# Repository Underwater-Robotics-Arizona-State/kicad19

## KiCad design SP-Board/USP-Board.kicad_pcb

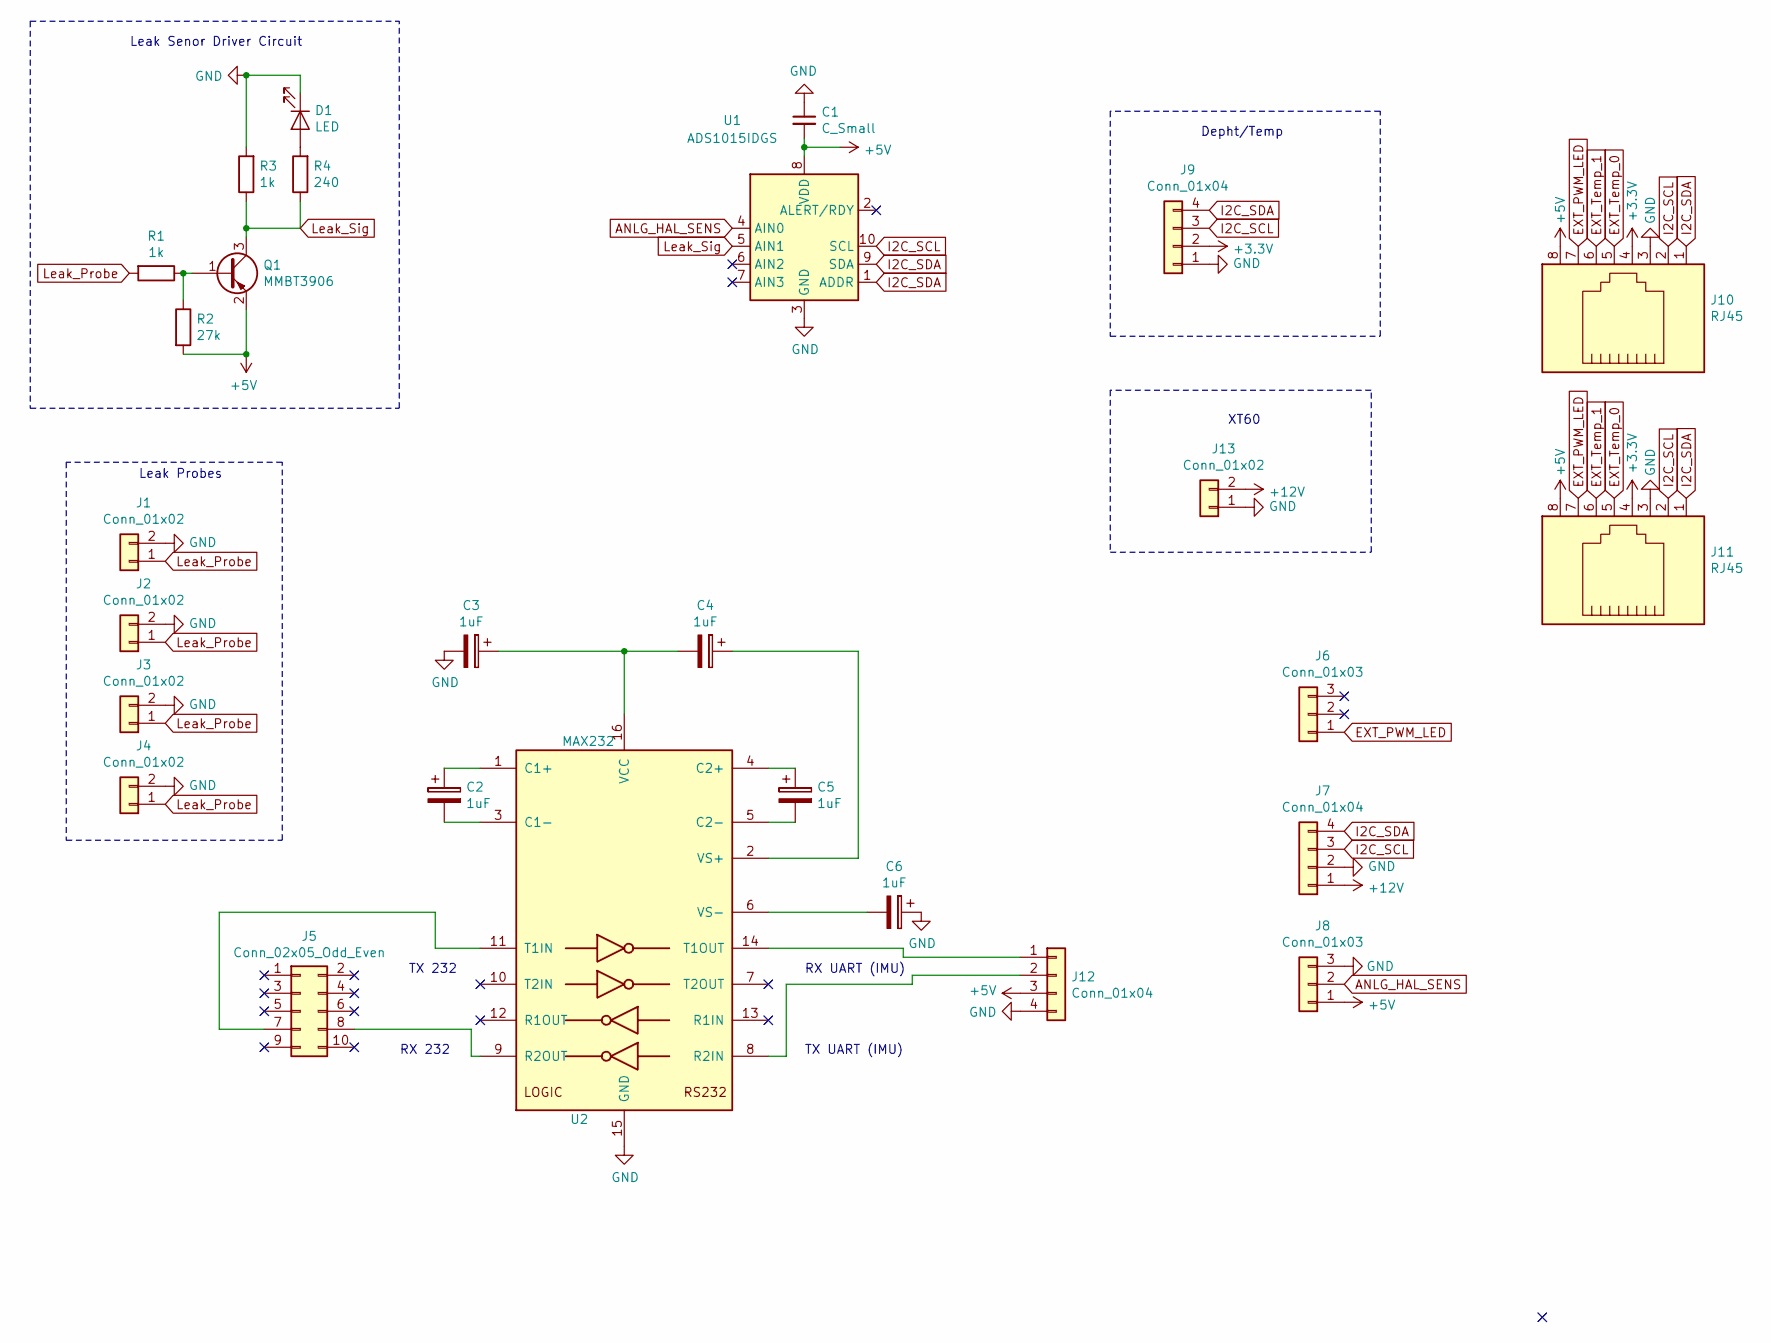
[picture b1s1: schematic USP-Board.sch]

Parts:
C1: C_Small; CP_EIA-1608-08_AVX-J_Pad1.25x1.05mm_HandSolder
C2, C3, C4, C5, C6: 1uF; CP_EIA-1608-08_AVX-J_Pad1.25x1.05mm_HandSolder
D1: LED; LED_0603_1608Metric
J1, J2, J3, J4: Conn_01x02; PinHeader_1x02_P2.54mm_Vertical
J5: Conn_02x05_Odd_Even; Amphenol 98424-G52-10LF
J6, J8: Conn_01x03; PinHeader_1x03_P2.54mm_Vertical
J7, J9, J12: Conn_01x04; PinHeader_1x04_P2.54mm_Vertical
J10, J11: RJ45; RJ45_8
J13: Conn_01x02; XT60
Q1: MMBT3906; SOT-23
R1, R3: 1k; R_1206_3216Metric_Pad1.42x1.75mm_HandSolder
R2: 27k; R_1206_3216Metric_Pad1.42x1.75mm_HandSolder
R4: 240; R_1206_3216Metric_Pad1.42x1.75mm_HandSolder
U1: ADS1015IDGS; TSSOP-10_3x3mm_P0.5mm
U2: MAX232; SOIC-16_3.9x9.9mm_P1.27mm

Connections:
+3V3: J9.2, J10.4, J11.4
+5V: C1.2, J8.1, J10.8, J11.8, J12.3, Q1.2 (E), R2.2, U1.8 (VDD)
+12V: J7.1, J13.2
ANLG_HAL_SENS: J8.2, U1.4 (AIN0)
EXT_PWM_LED: J6.1, J10.7, J11.7
EXT_Temp_0: J10.5, J11.5
EXT_Temp_1: J10.6, J11.6
GND: C1.1, C3.2, C6.1, D1.1 (K), J1.2, J2.2, J3.2, J4.2, J7.2, J8.3, J9.1, J10.3, J11.3, J12.4, J13.1, R3.2, U1.3 (GND), U2.15 (GND)
I2C_SCL: J7.3, J9.3, J10.2, J11.2, U1.10 (SCL)
I2C_SDA: J7.4, J9.4, J10.1, J11.1, U1.1 (ADDR), U1.9 (SDA)
Leak_Probe: J1.1, J2.1, J3.1, J4.1, R1.2
Leak_Sig: Q1.3 (C), R3.1, R4.1, U1.5 (AIN1)
unnamed: C2.1, U2.1 (C1+)
unnamed: C2.2, U2.3 (C1-)
unnamed: C3.1, C4.2, U2.16 (VCC)
unnamed: C4.1, U2.2 (VS+)
unnamed: C5.1, U2.4 (C2+)
unnamed: C5.2, U2.5 (C2-)
unnamed: C6.2, U2.6 (VS-)
unnamed: D1.2 (A), R4.2
unnamed: J5.7, U2.11 (T1IN)
unnamed: J5.8, U2.9 (R2OUT)
unnamed: J12.1, U2.14 (T1OUT)
unnamed: J12.2, U2.8 (R2IN)
unnamed: Q1.1 (B), R1.1, R2.1

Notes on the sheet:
Leak Senor Driver Circuit
Depht/Temp
XT60
Leak Probes
TX 232
RX 232
TX UART (IMU)
RX UART (IMU)

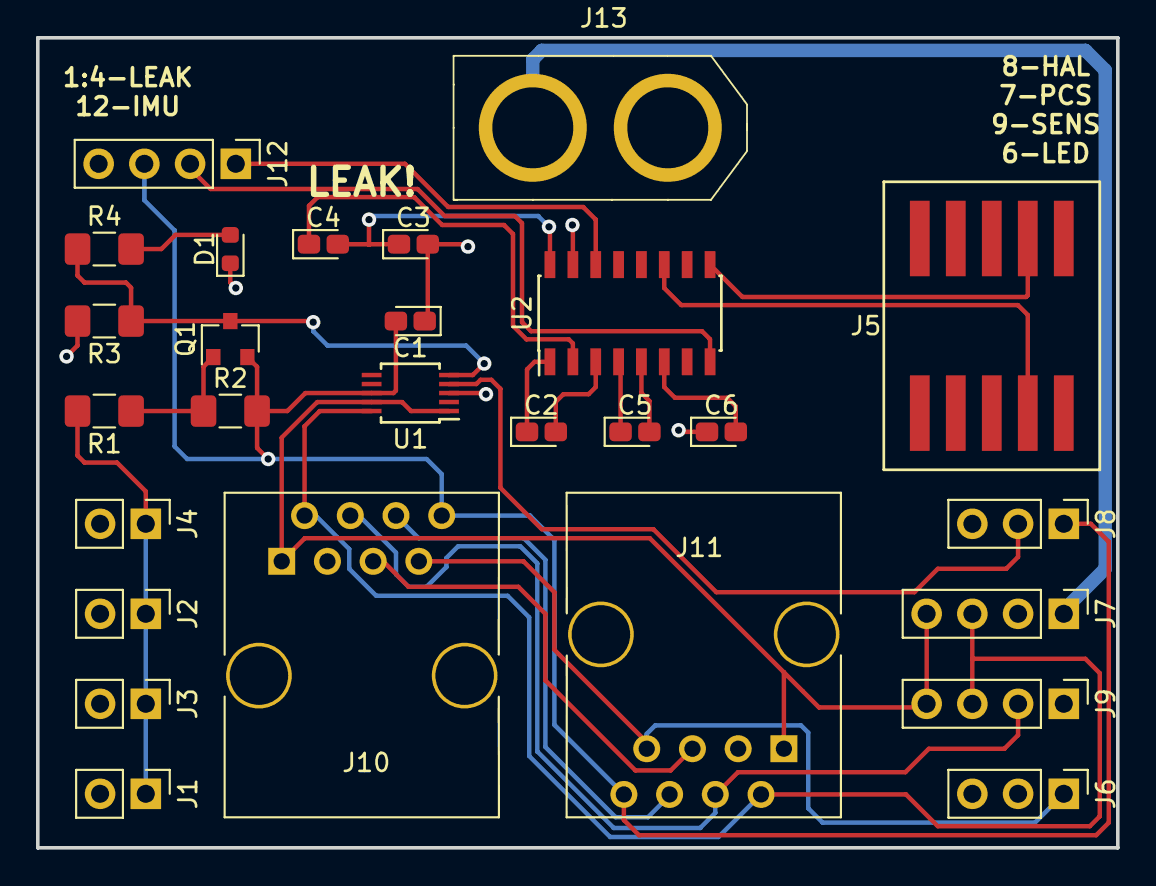
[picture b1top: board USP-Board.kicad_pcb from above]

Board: 2 copper layers, 60.0 x 45.0 mm, 27 parts (0 on the bottom side), 25 nets.

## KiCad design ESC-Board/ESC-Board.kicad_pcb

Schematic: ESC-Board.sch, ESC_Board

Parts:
A1: Arduino_Nano_v3.x; Arduino_Nano
F1, F2, F3, F4: 10/15; Fuse_SMD1206_HandSoldering
F5: 500m; Fuse_SMD1206_HandSoldering
I1, I2: RJ45; RJ45_8
J1, J2: Molex; Molex_6pin
J3: XT_60; XT60
MH1, MH2, MH3, MH4: MountingHole; MountingHole_3.2mm_M3
R1, R2: R; R_0805
U1, U2, U3, U4: ACS780xLRTR-100U; Allegro_PSOF-7_4.8x6.4mm_Pitch1.60mm
U5, U6, U7, U8: ESC:Blue_ESC; Blue_ESC
U9, U10: TMP235A2DBZT; SOT-23

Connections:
+3V3: A1.17, I1.4, I2.4, R1.1, R2.2, U9.1, U10.1
+5V: A1.27, I1.8, I2.8, U1.1 (VCC), U2.1 (VCC), U3.1 (VCC), U4.1 (VCC)
+12V: F1.2, F2.2, F3.2, F4.2, F5.1, J3.1
Current_A0: A1.21, U1.3 (VOUT)
Current_A1: A1.22, U2.3 (VOUT)
Current_A2: A1.23, U3.3 (VOUT)
Current_A3: A1.24, U4.3 (VOUT)
EXT_PWM_LED: A1.14, I1.7, I2.7
Ext_Temp_0: A1.26, I1.5, I2.5
Ext_Temp_1: A1.25, I1.6, I2.6
GND: A1.4, A1.29, I1.3, I2.3, J3.2, U1.2 (GND), U2.2 (GND), U3.2 (GND), U4.2 (GND), U5.2, U5.7, U6.2, U6.7, U7.2, U7.7, U8.2, U8.7, U9.3, U10.3
I2C_SCL: A1.8, I1.2, I2.2, R2.1
I2C_SDA: A1.7, I1.1, I2.1, R1.2
unnamed: A1.30, F5.2
unnamed: F1.1, U1.6 (IP-)
unnamed: F2.1, U2.6 (IP-)
unnamed: F3.1, U3.6 (IP-)
unnamed: F4.1, U4.6 (IP-)
unnamed: J1.1, U5.5
unnamed: J1.2, U5.4
unnamed: J1.3, U5.3
unnamed: J1.4, U6.5
unnamed: J1.5, U6.4
unnamed: J1.6, U6.3
unnamed: J2.1, U7.5
unnamed: J2.2, U7.4
unnamed: J2.3, U7.3
unnamed: J2.4, U8.5
unnamed: J2.5, U8.4
unnamed: J2.6, U8.3
PWM_ESC_1: A1.13, U8.6
PWM_ESC_2: A1.12, U7.6
PWM_ESC_3: A1.9, U6.6
PWM_ESC_4: A1.6, U5.6
Power_ESC_1: U1.5 (IP+), U8.1
Power_ESC_2: U2.5 (IP+), U7.1
Power_ESC_3: U3.5 (IP+), U6.1
Power_ESC_4: U4.5 (IP+), U5.1
Temp_A4: A1.20, U9.2
Temp_A5: A1.19, U10.2

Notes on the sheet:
Power Connector
Ardunio Nano
I2C RJ45 Connector
Current Monintoring
ESC to Connectors
Mounting Holes
Tempure Sensors

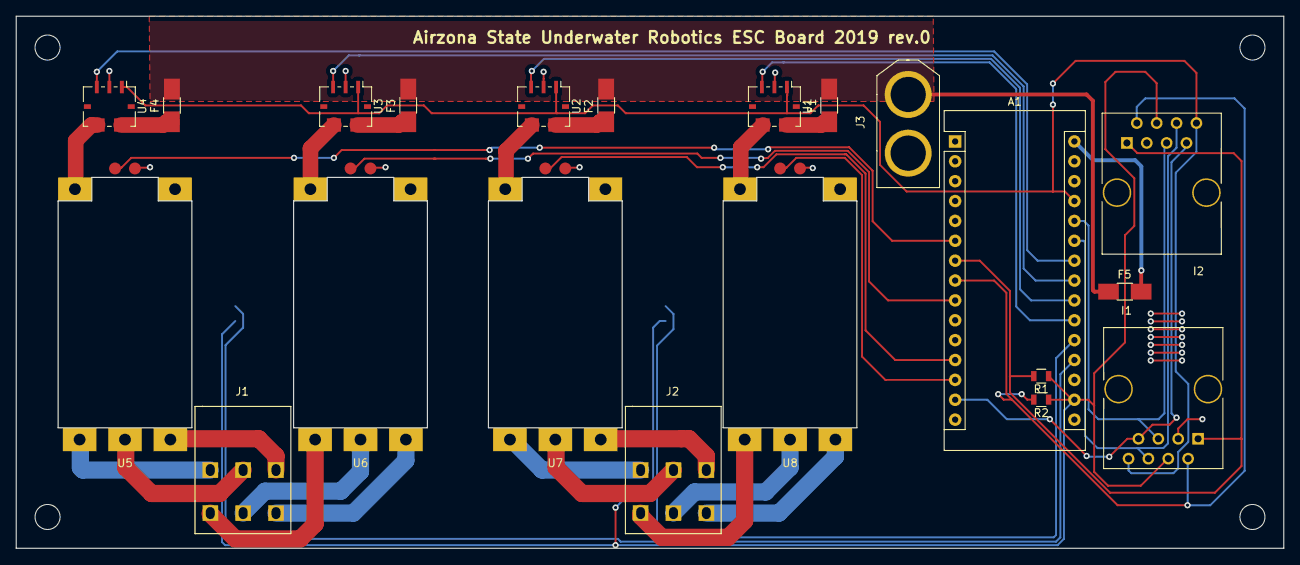
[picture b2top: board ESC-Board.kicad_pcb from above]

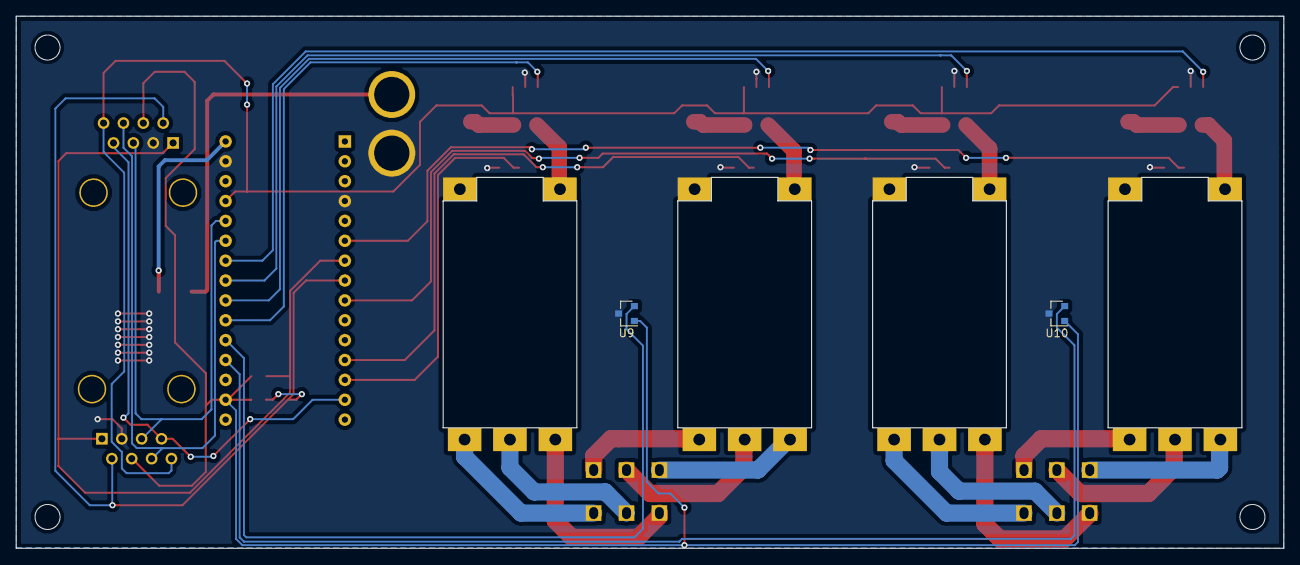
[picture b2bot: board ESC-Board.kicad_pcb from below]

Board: 2 copper layers, 162.0 x 68.0 mm, 28 parts (2 on the bottom side), 40 nets.

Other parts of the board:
 MH3: MountingHole; MountingHole_3.2mm_M3

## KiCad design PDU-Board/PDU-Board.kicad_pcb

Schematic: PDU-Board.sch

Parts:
J0: Main Feed; XT60
J1: Motor-1; XT60
J2: Motor-2; XT60
J3: Mother Board; XT60
J4, J5: RJ45; RJ45_8
U1, U2, U3, U4: VICOR-DC-DC; VICOR_VIA_DCM3414
U5, U6: ESC:TMP235A2DBZT; SOT-23

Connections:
48v_GND: J0.2, U1.2, U2.2, U3.2, U4.2
+3V3: J4.4, J5.4, U5.1, U6.1
+12V: J1.1, J2.1, J3.1, U1.3, U2.3, U3.3, U4.3
+48V: J0.1, U1.1, U2.1, U3.1, U4.1
Ext_Temp_0: J4.5, J5.5, U6.2
Ext_Temp_1: J4.6, J5.6, U5.2
GND: J1.2, J2.2, J3.2, J4.3, J5.3, U1.4, U2.4, U3.4, U4.4, U5.3, U6.3
unnamed: J4.1, J5.1
unnamed: J4.2, J5.2
unnamed: J4.8, J5.8
Water_Sensor: J4.7, J5.7

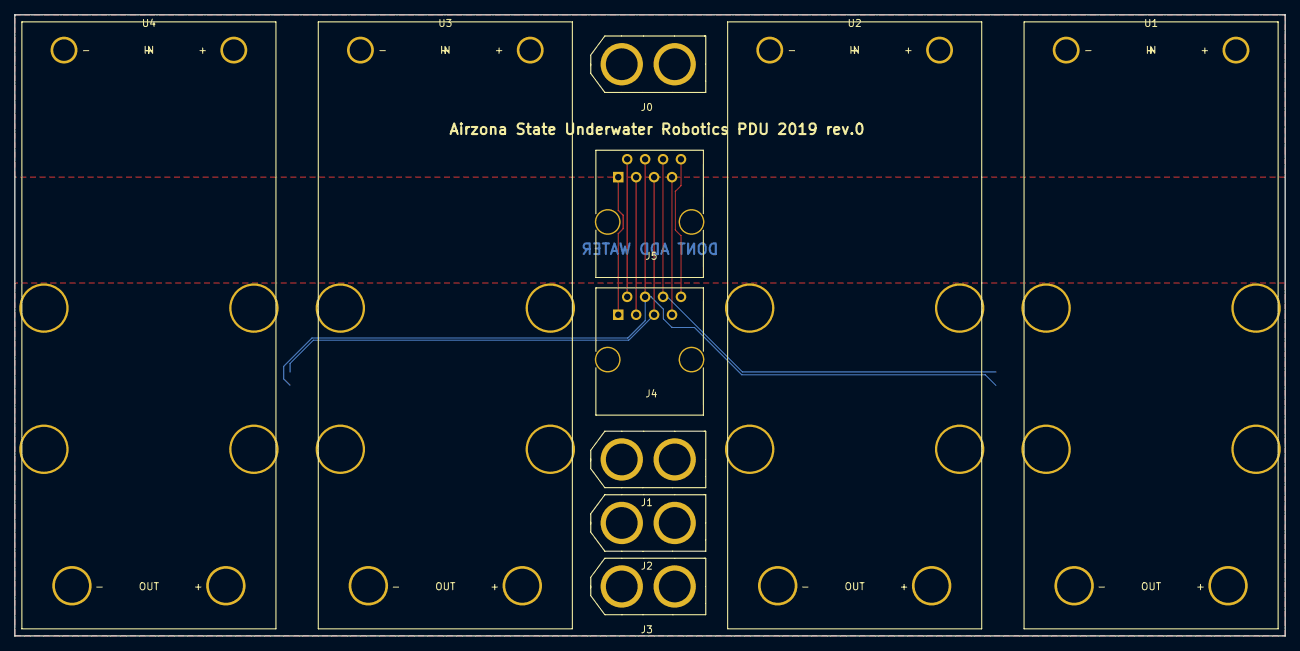
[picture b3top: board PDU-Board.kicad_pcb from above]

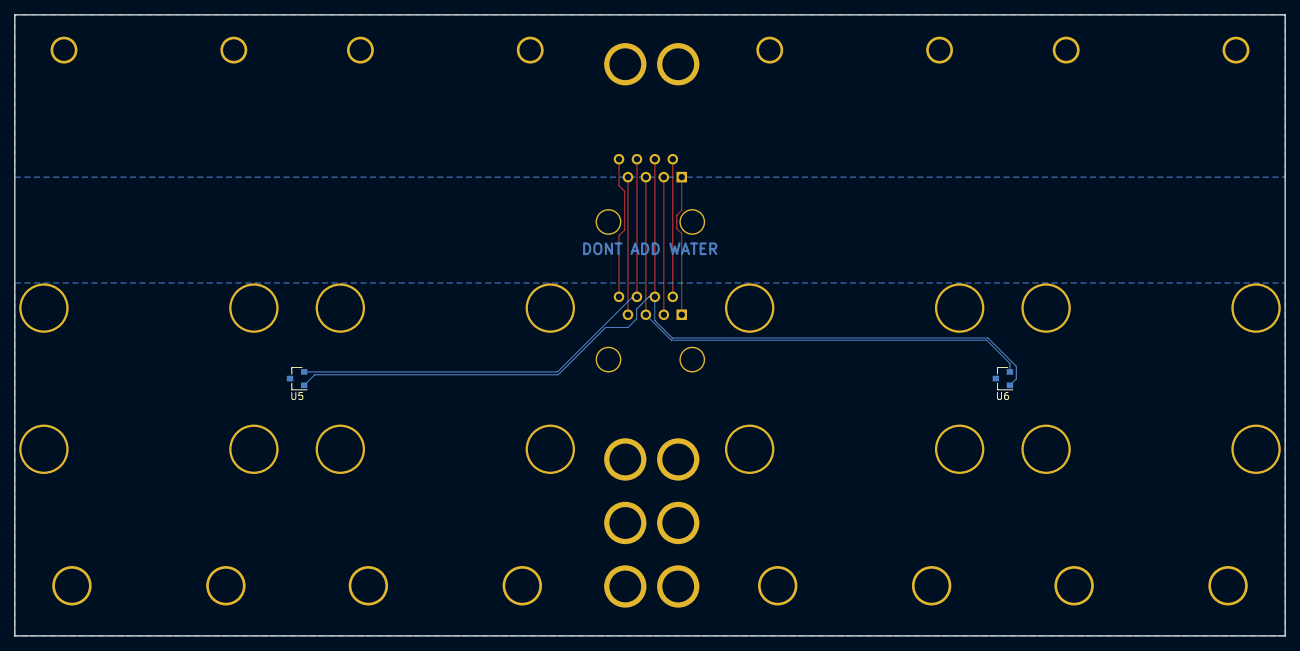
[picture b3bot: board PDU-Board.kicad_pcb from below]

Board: 2 copper layers, 180.0 x 88.0 mm, 12 parts (2 on the bottom side), 11 nets.

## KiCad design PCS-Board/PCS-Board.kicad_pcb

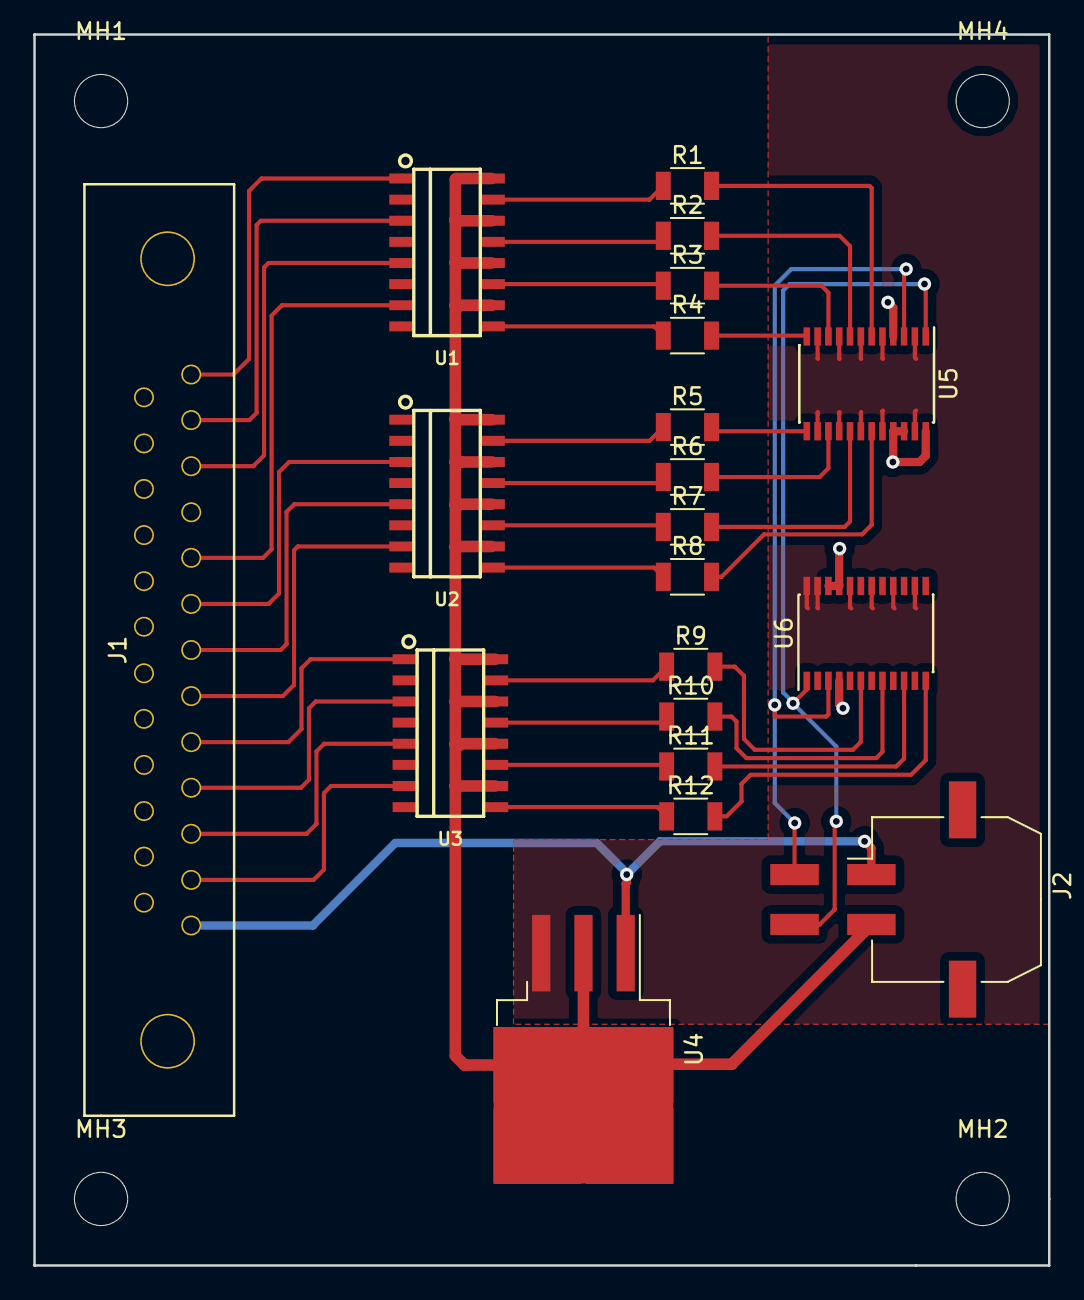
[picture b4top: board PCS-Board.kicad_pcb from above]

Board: 2 copper layers, 61.0 x 74.0 mm, 24 parts (0 on the bottom side), 40 nets.

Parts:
J1: DB25_Female_MountingHoles; Dsub 25pin
J2: Conn_01x04; Molex_MicroFit_3.0-43045-0410_04x3.00mm_Angled
MH1, MH2, MH3, MH4: MountingHole; MountingHole_3.2mm_M3
R1, R2, R3, R4, R5, R6, R7, R8, R9, R10, R11, R12: R; R_1206
U1, U2, U3: MMPQ2222A; Soc-16
U4: uA7805; TO-263-3_TabPin2
U5, U6: ADG715; TSSOP-24

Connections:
+5V: U4.3, U5.2, U5.5, U5.7, U5.9, U5.11, U5.14, U5.16, U5.18, U5.20, U5.23, U6.2, U6.5, U6.7, U6.9, U6.11, U6.14, U6.16, U6.18, U6.20, U6.23, U6.24
+12V: J1.13, J2.1, U4.1
GND: J2.2, U1.10, U1.12, U1.14, U1.16, U2.10, U2.12, U2.14, U2.16, U3.10, U3.12, U3.14, U3.16, U4.2, U5.4, U5.21, U5.22, U5.24, U6.4, U6.21, U6.22
I2C_SCL: J2.3, U5.1, U6.1
I2C_SDA: J2.4, U5.3, U6.3
unnamed: R1.1, U1.15
unnamed: R2.1, U1.13
unnamed: R3.1, U1.11
unnamed: R4.1, U1.9
unnamed: R5.1, U2.15
unnamed: R6.1, U2.13
unnamed: R7.1, U2.11
unnamed: R8.1, U2.9
unnamed: R9.1, U3.15
unnamed: R10.1, U3.13
unnamed: R11.1, U3.11
unnamed: R12.1, U3.9
SOLN_EN0: R1.2, U5.6
SOLN_EN1: R2.2, U5.8
SOLN_EN2: R3.2, U5.10
SOLN_EN3: R4.2, U5.12
SOLN_EN4: R5.2, U5.13
SOLN_EN5: R6.2, U5.15
SOLN_EN6: R7.2, U5.17
SOLN_EN7: R8.2, U5.19
SOLN_EN8: R9.2, U6.6
SOLN_EN9: R10.2, U6.8
SOLN_EN10: R11.2, U6.10
SOLN_EN11: R12.2, U6.12
SOLN_PW0: J1.1, U1.1
SOLN_PW1: J1.2, U1.3
SOLN_PW2: J1.3, U1.5
SOLN_PW4: J1.5, U1.7
SOLN_PW5: J1.6, U2.3
SOLN_PW6: J1.7, U2.5
SOLN_PW7: J1.8, U2.7
SOLN_PW8: J1.9, U3.1
SOLN_PW9: J1.10, U3.3
SOLN_PW10: J1.11, U3.5
SOLN_PW11: J1.12, U3.7

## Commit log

2018-12-27 First Upload
2018-12-27 File Path Fix
2018-12-27 colton fix
    schematic issues
2018-12-27 added 3414 and nano footprint and removed gerbers
2018-12-27 little fixes on PDB
2018-12-30 basic fix
2018-12-30 Second Draft (in progress)
    Starting clean up of sch
2018-12-30 Second Draft(In Progress) v2
2018-12-30 Second Draft(in progess) v3
2018-12-30 Second Draft(Final version)
    Alex pls
2018-12-31 Final Draft
2018-12-31 Final Draft(with net list)
2018-12-31 Starting layout
2019-01-03 I hate myself
2019-01-03 OOOF
2019-01-03 Big PP
2019-01-03 Better footprint
    I likey
2019-01-03 Fixed ESC Pwm lines
2019-01-03 More ESC fixes
2019-01-03 ESC Fixes
2019-01-03 Mounting holes
    I did a think
2019-01-03 Layout Draft(Final)
    Needs wires
2019-01-03 Final Layout needs routering
2019-01-03 Foot print fixes
2019-01-03 Added Vicor footprint
    eeeeeeeeeeeeeeeeeeeeeeeeee
2019-01-03 Make Gerberals go bye bye
2019-01-03 PDU Board work
2019-01-04 Board Finalized
    E
2019-01-04 Added Step
2019-01-04 Need current pushed up
2019-01-04 Moved Current sensors up
2019-01-04 ESC board Finalized ready for production
2019-01-04 Fixed names
2019-01-04 Fix issues with ERC
2019-01-04 More fixes on traces
2019-01-04 Fix scmatic
2019-01-05 Fixed issue with scl line
2019-01-05 Begun PDU layout
2019-01-07 temp senors added not finised
2019-01-07 Finalzed Boards ready for production
    YEah
2019-01-08 Added pneumatic files to master
2019-01-08 PCS inital design
2019-01-08 PCS Sch update
2019-01-08 PCS Sch cleanup
    No changes to sch just cleaning it up
2019-01-11 Update to PCS sch
2019-01-11 Fixed Molex hole issue
    Squares dont go in circle holes
2019-01-11 Fix more molex issues
2019-01-11 Forgot to leave fills on
2019-01-18 Add gates
2019-01-18 Alex is big ghey
2019-01-18 Added BJT to SCH
2019-01-18 Fixed RJ 45 connector
2019-01-24 Fixed PDU footprint isuess
    vicor foot print fixed
2019-01-24 Added Drill files and fixed holes
2019-01-24 Add pdu step
2019-01-24 PCS Sch updated with dsub connectorr
2019-01-28 Re designed PDU pre mec spec
2019-01-28 Fixed slik
2019-01-28 Fixed sch on PCS crash
2019-01-28 PDU updated
2019-01-28 Added Dsub footprint
2019-01-28 Began work on pcs board
2019-01-30 Moving to destop
2019-01-30 Wiring has begun Im dead inside
2019-01-30 More wiring and sadness
2019-02-01 Big oof
2019-02-01 Finalized the Wiring for PCS
2019-02-03 Updated PDU and ESC for leak sensor
2019-02-06 Added 5v
2019-02-07 Started Utilltiy sensor packages Board (If you think of a better name lmk)
2019-02-09 Finalized
2019-02-13 Messing with sch
2019-02-20 Worked on USp Sch needs more work
2019-02-21 Renamed USP to SP
2019-02-21 Added Leak probe connectors and xt60 connector
2019-02-22 moving macines
2019-02-22 Udated ADC 90% complete
2019-03-16 test code
2019-03-16 Motor_driver_Software.ino
    Began work on main loop and speed control function
2019-03-16 Revert "Motor_driver_Software.ino"
    This reverts commit 50046fc6471398c588cb632a5e79dd2276c2a5ba.
2019-03-16 Revert "Revert "Motor_driver_Software.ino""
    This reverts commit a36216e09219449769cfd6fc40605f35dbec744d.
2019-03-16 Began main loop and ESC speed function
2019-03-24 backup
2019-03-26 More sch updates
2019-03-26 Early Footprint
2019-04-01 moving to desktop
2019-04-01 eeeeeeeee
2019-04-09 Assigining footprints
    eeeeeeeeeeeeeeeeeeeeeeeeeeeeeeeeeeeeeeeeeeeeeeeeeeeeeeeeee
2019-04-10 moving to pc
2019-04-10 Needs wires board layout 95%
2019-04-10 added xt60
2019-04-10 com board prelim is finaly done
2019-04-11 wiring done
2019-04-13 current
